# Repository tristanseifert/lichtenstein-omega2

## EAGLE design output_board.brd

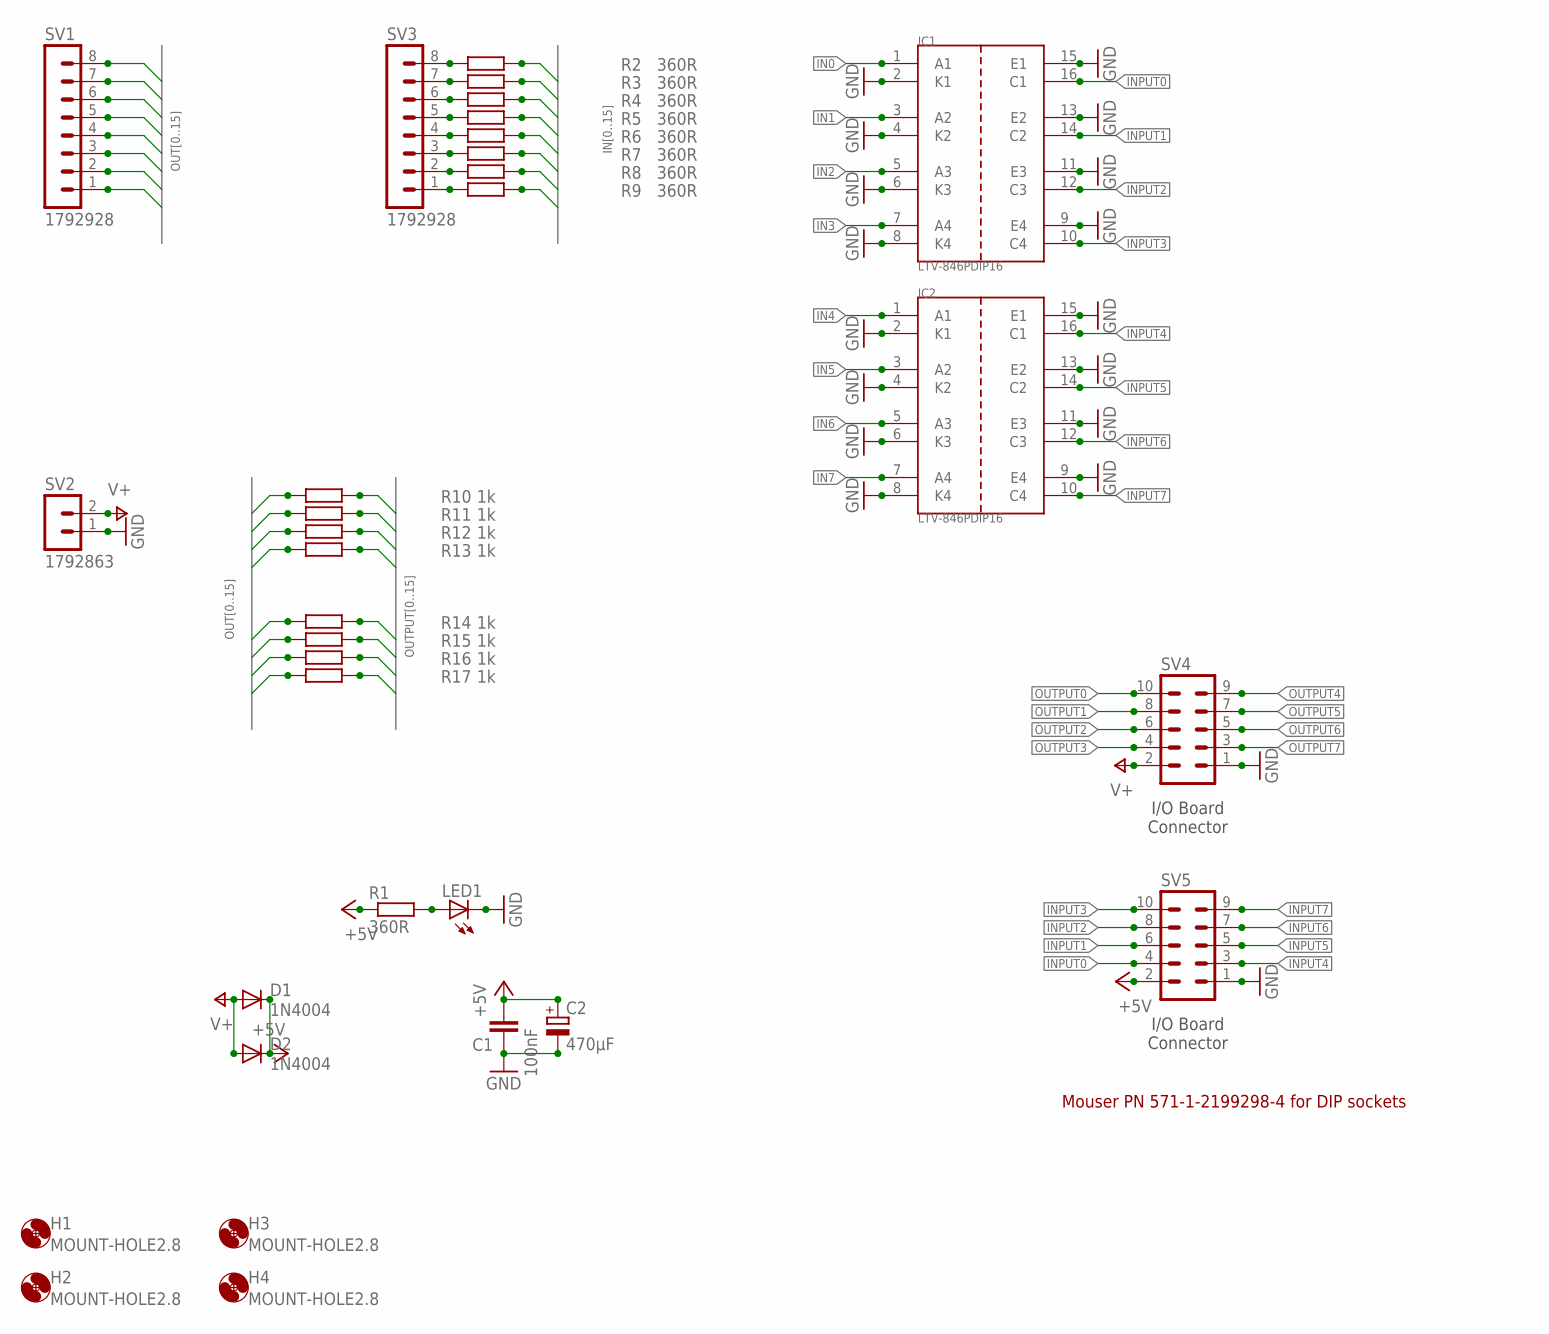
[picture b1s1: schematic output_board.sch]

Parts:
C1: 100nF; C0805; MOUSER 710-885012207072
C2: 470µF; E5-10,5; MOUSER 598-477CKH016M
D1, D2: 1N4004; DO41-10; MOUSER 833-1N4004-TP
H1, H2, H3, H4: MOUNT-HOLE2.8; 2,8
IC1, IC2: LTV-846PDIP16; DIL16; MOUSER 859-LTV-846
LED1: LEDCHIPLED_1206; CHIPLED_1206; MOUSER 604-APTR3216YC
R1, R2, R3, R4, R5, R6, R7, R8, R9: 360R; M0805; MOUSER 652-CR0805JW-361ELF
R10, R11, R12, R13, R14, R15, R16, R17: 1k; M0805; MOUSER 652-CR0805JW-102ELF
SV1, SV3: 1792928; MOUSER 651-1792928
SV2: 1792863
SV4, SV5: MA05-2; MOUSER 517-30310-6002

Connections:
+5V: C1.2, C2.+, D1.C, D2.C, R1.1, SV5.2
GND: C1.1, C2.-, IC1.2 (K1), IC1.4 (K2), IC1.6 (K3), IC1.8 (K4), IC1.9 (E4), IC1.11 (E3), IC1.13 (E2), IC1.15 (E1), IC2.2 (K1), IC2.4 (K2), IC2.6 (K3), IC2.8 (K4), IC2.9 (E4), IC2.11 (E3), IC2.13 (E2), IC2.15 (E1), LED1.C, SV2.1, SV4.1, SV5.1
IN0: IC1.1 (A1), R9.2
IN1: IC1.3 (A2), R8.2
IN2: IC1.5 (A3), R7.2
IN3: IC1.7 (A4), R6.2
IN4: IC2.1 (A1), R5.2
IN5: IC2.3 (A2), R4.2
IN6: IC2.5 (A3), R3.2
IN7: IC2.7 (A4), R2.2
INPUT0: IC1.16 (C1), SV5.4
INPUT1: IC1.14 (C2), SV5.6
INPUT2: IC1.12 (C3), SV5.8
INPUT3: IC1.10 (C4), SV5.10
INPUT4: IC2.16 (C1), SV5.3
INPUT5: IC2.14 (C2), SV5.5
INPUT6: IC2.12 (C3), SV5.7
INPUT7: IC2.10 (C4), SV5.9
unnamed: LED1.A, R1.2
unnamed: R2.1, SV3.8
unnamed: R3.1, SV3.7
unnamed: R4.1, SV3.6
unnamed: R5.1, SV3.5
unnamed: R6.1, SV3.4
unnamed: R7.1, SV3.3
unnamed: R8.1, SV3.2
unnamed: R9.1, SV3.1
OUT0: R10.1, SV1.1
OUT1: R11.1, SV1.2
OUT2: R12.1, SV1.3
OUT3: R13.1, SV1.4
OUT4: R14.1, SV1.5
OUT5: R15.1, SV1.6
OUT6: R16.1, SV1.7
OUT7: R17.1, SV1.8
OUTPUT0: R10.2, SV4.10
OUTPUT1: R11.2, SV4.8
OUTPUT2: R12.2, SV4.6
OUTPUT3: R13.2, SV4.4
OUTPUT4: R14.2, SV4.9
OUTPUT5: R15.2, SV4.7
OUTPUT6: R16.2, SV4.5
OUTPUT7: R17.2, SV4.3
V+: D1.A, D2.A, SV2.2, SV4.2

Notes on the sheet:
I/O Board Connector
Mouser PN 571-1-2199298-4 for DIP sockets

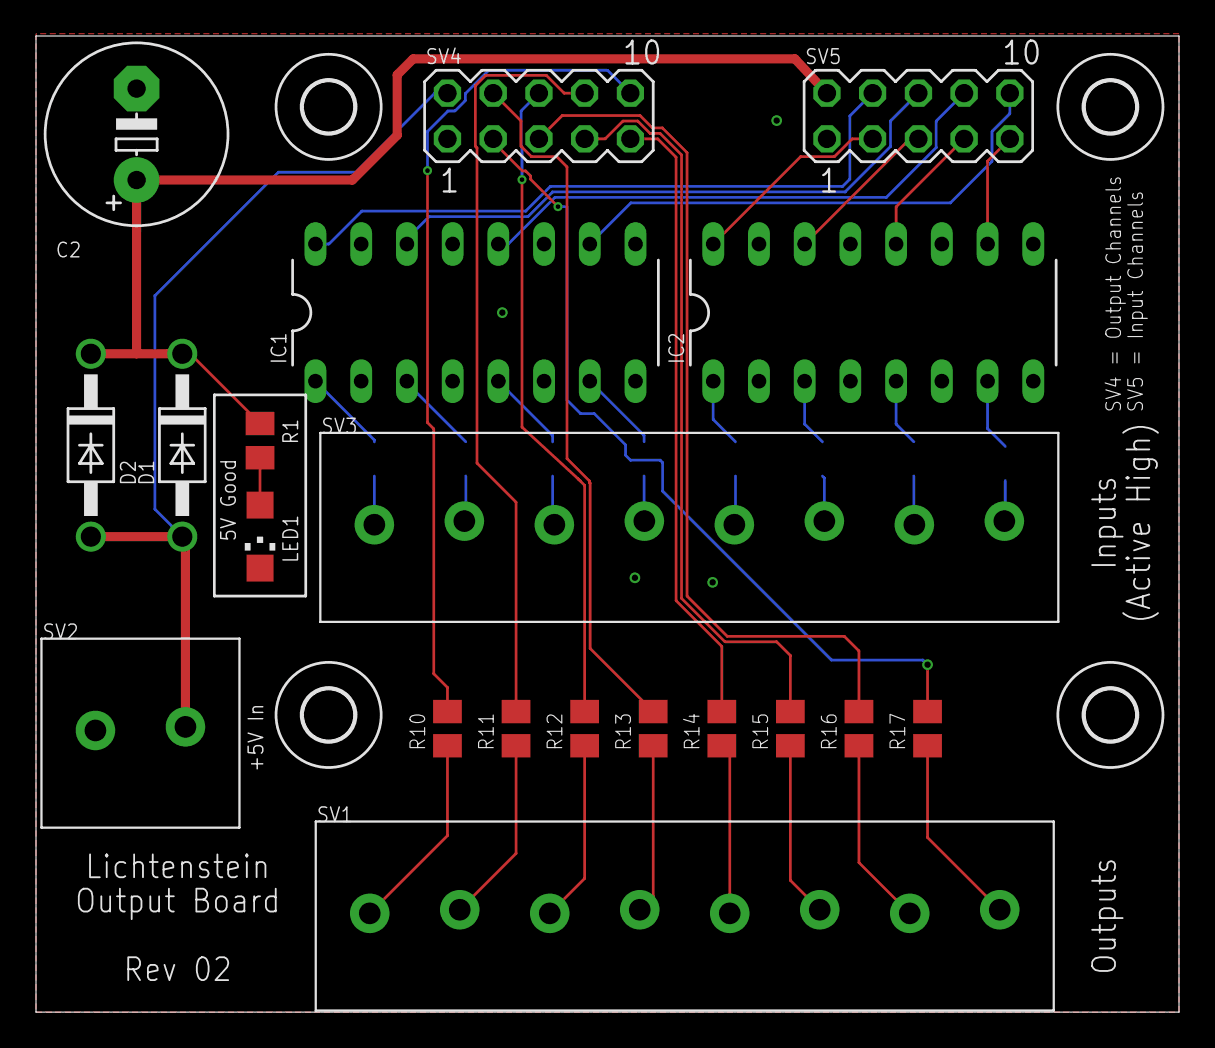
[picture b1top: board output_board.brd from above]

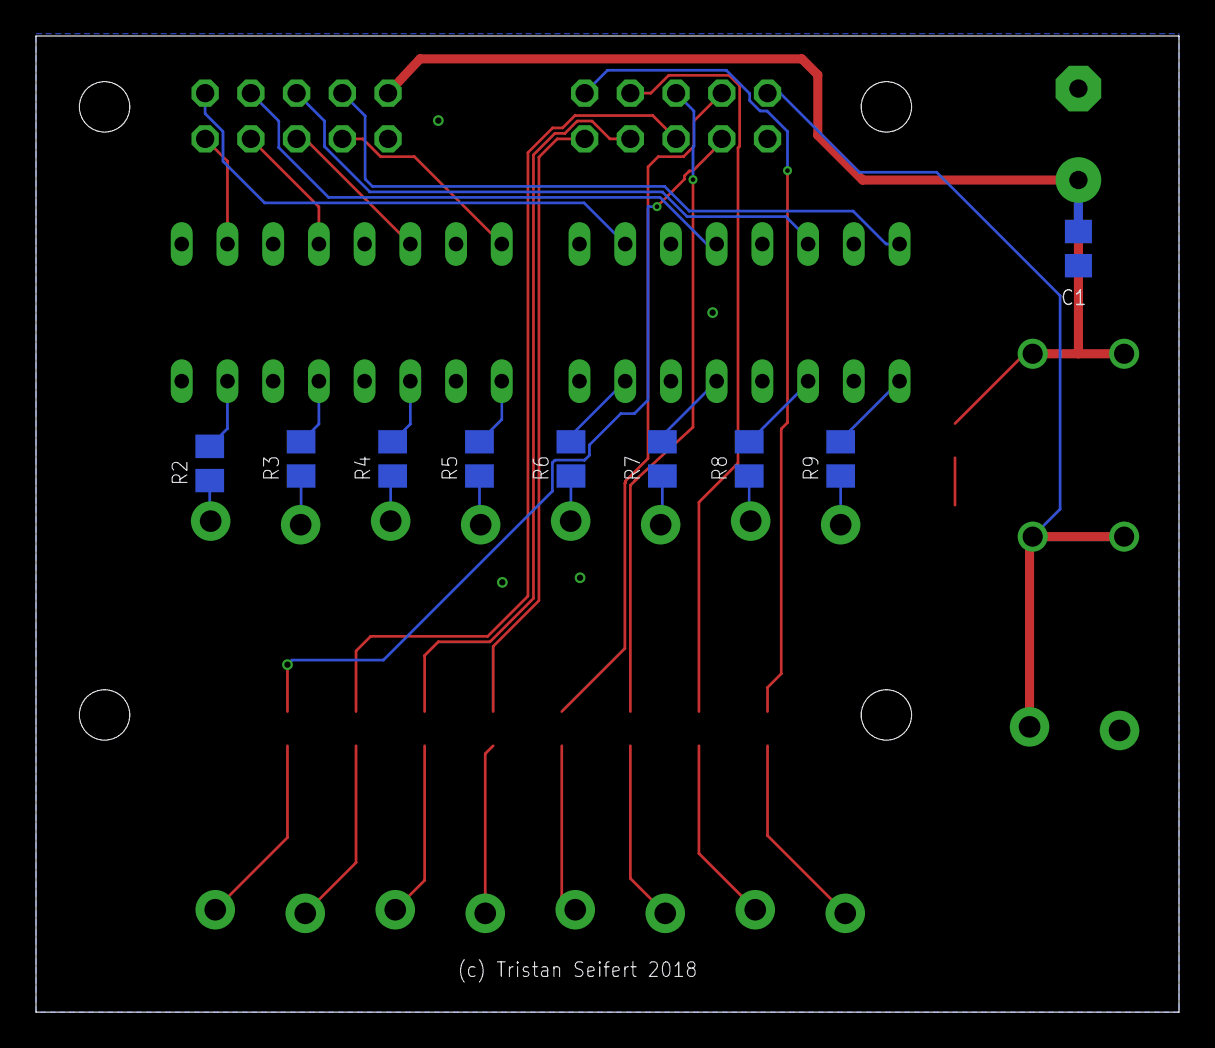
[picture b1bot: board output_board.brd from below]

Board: 2 copper layers, 63.5 x 54.2 mm, 33 parts (9 on the bottom side), 44 nets.

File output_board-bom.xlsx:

Partlist exported from /Users/tristan/EAGLE/lichtenstein-omega2/output_board.sc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
Part | Value | Device | Package | Description | MOUSER
C1 | 100nF | C-EUC0805 | C0805 | CAPACITOR, European symbol | 710-885012207072
C2 | 470µF | CPOL-EUE5-13 | E5-13 | POLARIZED CAPACITOR, European symbol | 598-477CKH016M
D1 | 1N4004 | 1N4004 | DO41-10 | DIODE | 833-1N4004-TP
D2 | 1N4004 | 1N4004 | DO41-10 | DIODE | 833-1N4004-TP
IC1 | LTV-846PDIP16 | LTV-846PDIP16 | DIL16 | LTV-846 – 4 Channel Optocoupler | 859-LTV-846
IC2 | LTV-846PDIP16 | LTV-846PDIP16 | DIL16 | LTV-846 – 4 Channel Optocoupler | 859-LTV-846
LED1 |  | LEDCHIPLED_1206 | CHIPLED_1206 | LED | 604-APTR3216YC
R1 | 360R | R-EU_M0805 | M0805 | RESISTOR, European symbol | 652-CR0805JW-361ELF
R2 | 360R | R-EU_M0805 | M0805 | RESISTOR, European symbol | 652-CR0805JW-361ELF
R3 | 360R | R-EU_M0805 | M0805 | RESISTOR, European symbol | 652-CR0805JW-361ELF
R4 | 360R | R-EU_M0805 | M0805 | RESISTOR, European symbol | 652-CR0805JW-361ELF
R5 | 360R | R-EU_M0805 | M0805 | RESISTOR, European symbol | 652-CR0805JW-361ELF
R6 | 360R | R-EU_M0805 | M0805 | RESISTOR, European symbol | 652-CR0805JW-361ELF
R7 | 360R | R-EU_M0805 | M0805 | RESISTOR, European symbol | 652-CR0805JW-361ELF
R8 | 360R | R-EU_M0805 | M0805 | RESISTOR, European symbol | 652-CR0805JW-361ELF
R9 | 360R | R-EU_M0805 | M0805 | RESISTOR, European symbol | 652-CR0805JW-361ELF
R10 | 1k | R-EU_M0805 | M0805 | RESISTOR, European symbol | 652-CR0805JW-102ELF
R11 | 1k | R-EU_M0805 | M0805 | RESISTOR, European symbol | 652-CR0805JW-102ELF
R12 | 1k | R-EU_M0805 | M0805 | RESISTOR, European symbol | 652-CR0805JW-102ELF
R13 | 1k | R-EU_M0805 | M0805 | RESISTOR, European symbol | 652-CR0805JW-102ELF
R14 | 1k | R-EU_M0805 | M0805 | RESISTOR, European symbol | 652-CR0805JW-102ELF
R15 | 1k | R-EU_M0805 | M0805 | RESISTOR, European symbol | 652-CR0805JW-102ELF
R16 | 1k | R-EU_M0805 | M0805 | RESISTOR, European symbol | 652-CR0805JW-102ELF
R17 | 1k | R-EU_M0805 | M0805 | RESISTOR, European symbol | 652-CR0805JW-102ELF
SV1 | 1792928 | 1792928 | 1792928 | PCB terminal block - PTS 1,5/ 8-5,0-H - 1792928 | 651-1792928
SV2 | 1792863 | 1792863 | 1792863 | PCB terminal block - PTS 1,5/ 2-5,0-H - 1792863 | 651-1792863
SV3 | 1792928 | 1792928 | 1792928 | PCB terminal block - PTS 1,5/ 8-5,0-H - 1792928 | 651-1792928
SV4 |  | MA05-2 | MA05-2 | PIN HEADER | 517-30310-6002
SV5 |  | MA05-2 | MA05-2 | PIN HEADER | 517-30310-6002
SOCK1 |  |  | DIL16 | 16-pin DIP socket | 571-1-2199298-4
SOCK2 |  |  | DIL16 | 16-pin DIP socket | 571-1-2199298-4
